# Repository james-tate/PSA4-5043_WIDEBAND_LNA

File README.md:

#PSA4-5043 LNA with onboard Bias tee designed for use with RTL SDR dongles, hackrf, or other SDR. LNA has two power options, USB mini or power from inline. There is also an option for an on-board wideband bias tee and bandpass filter.

"The current board design needs a series resistor between J1 and LED1 in order for the LED to operate. I will redesign the board soon to accommodate the changes. If you have the current board design, the trace can be cut betweeen the components and a 470ohm resistor can be put in its place."

[PSA4-5043 ](http://www.minicircuits.com/pdfs/PSA4-5043+.pdf) -- .05 to 4GHz  

[TCBT-14+ Bias Tee](http://www.minicircuits.com/pdfs/TCBT-14+.pdf) -- 10MHz to 10GHz  

[Optional bandpass filter](http://www.minicircuits.com/products/filters_sm_bandpass.shtml). 

<a href="https://oshpark.com/shared_projects/NCNWYLgf"></img></a> You can order the 3 copies of the board from Oshpark for $4.75 

Feel free to contact me  if any questions or if you suggest changes.

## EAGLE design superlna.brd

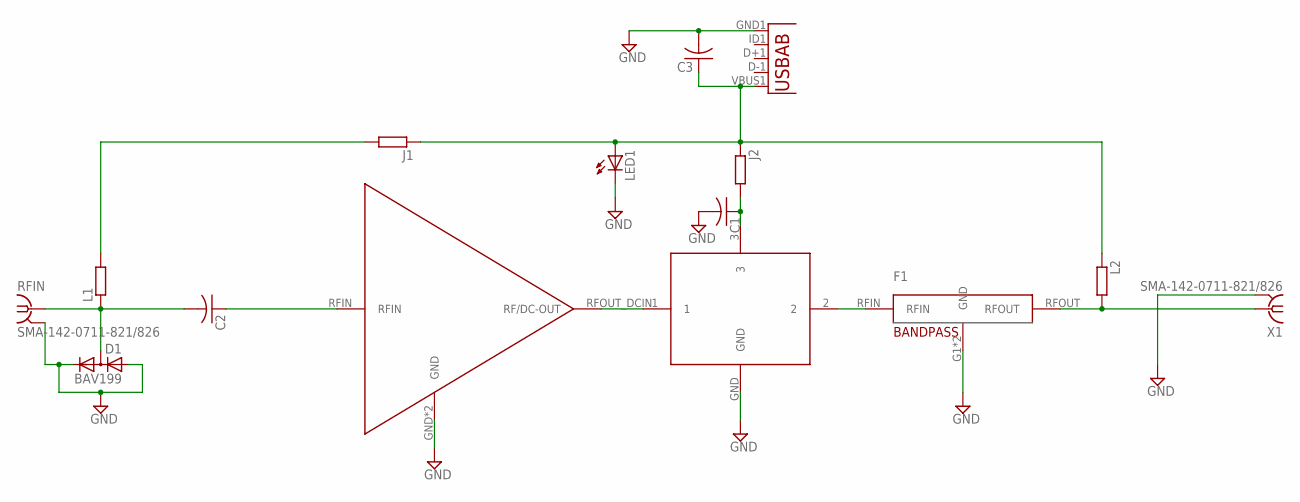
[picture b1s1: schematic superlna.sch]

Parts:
C1, C2, C3: C-USC0402; C0402
D1: BAV199; SOT23
F1: BANDPASS; FV1206
J1, J2: R-EU_R0805; R0805
L1, L2: R-EU_R0805; R0805
LED1: LED_ESML0603; LED_SML0603
LNA: AMP; SOC-343
POWER: USB""; USB-MICRO-SMD
RFIN: SMA-142-0711-821/826; J502-ND-142-0711-821/826
U1: BIASTEE; GU1414
X1: SMA-142-0711-821/826; J502-ND-142-0711-821/826

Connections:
BIASPOWER: C1.1, J2.2, U1.3
GND: C1.2, C3.2, D1.1 (A), D1.2 (C), F1.G1 (GND), F1.G2 (GND), LED1.C, LNA.GND, LNA.GND1 (GND), POWER.GND1 (GND), RFIN.G@1 (2), RFIN.G@2 (2), RFIN.G@3 (2), RFIN.G@4 (2), U1.GND, X1.G@1 (2), X1.G@2 (2), X1.G@3 (2), X1.G@4 (2)
unnamed: C2.1, LNA.RFIN
unnamed: LNA.RFOUT_DCIN (RF/DC-OUT), U1.1
unnamed: J1.2, L1.2
PWRIN: C3.1, J1.1, J2.1, L2.1, LED1.A, POWER.VBUS1 (VBUS)
RFIN: C2.2, D1.3 (AC), L1.1, RFIN.1
RFOUT: F1.RFOUT, L2.2, X1.1
RFOUT1: F1.RFIN, U1.2

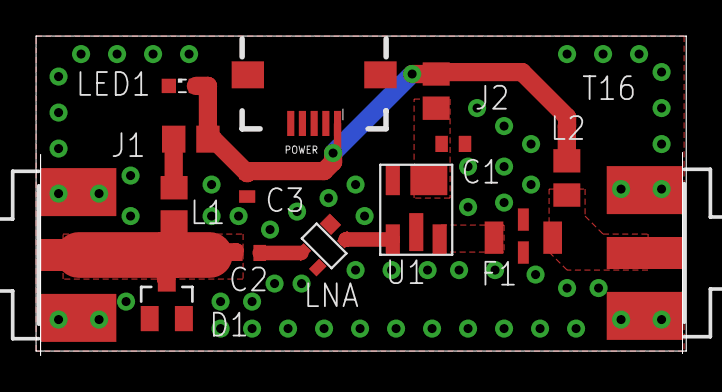
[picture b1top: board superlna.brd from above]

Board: 2 copper layers, 36.1 x 17.7 mm, 15 parts (0 on the bottom side), 9 nets.

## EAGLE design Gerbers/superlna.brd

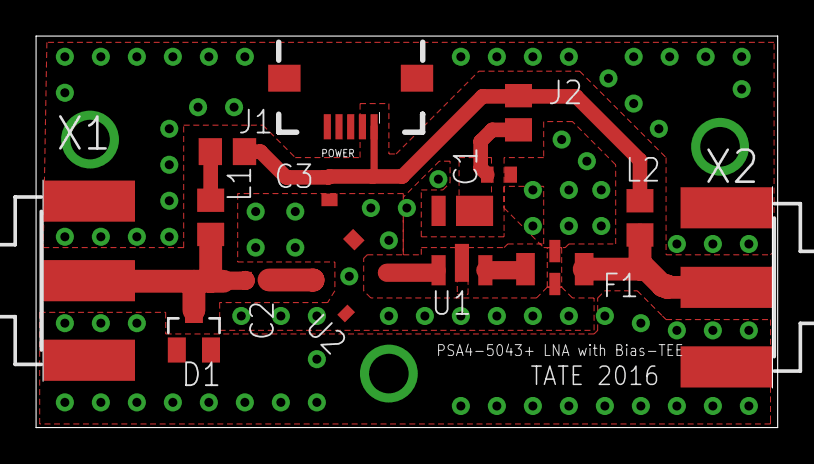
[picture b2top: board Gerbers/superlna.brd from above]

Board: 2 copper layers, 41.2 x 21.8 mm, 14 parts (0 on the bottom side), 9 nets.

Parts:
C1, C2, C3: C0402
D1: BAV199; SOT23
F1: BANDPASS; FV1206
J1, J2: R0805
L1, L2: R0805
POWER: USB-MICRO-SMD
U1: BIASTEE; GU1414
U2: AMP; SOC-343
X1, X2: SMA-142-0701-801/806; J502-ND-142-0701-801/806

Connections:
BIASPOWER: C1.1, J2.2, U1.3
GND: C1.2, C3.2, D1.1, D1.2, F1.G1, F1.G2, POWER.GND1, U1.GND, U2.GND, U2.GND1, X1.G@1, X1.G@2, X1.G@3, X1.G@4, X2.G@1, X2.G@2, X2.G@3, X2.G@4
unnamed: C2.1, U2.RFIN
unnamed: C3.1, J1.1, J2.1, L2.1, POWER.VBUS1
unnamed: U1.1, U2.RFOUT_DCIN
unnamed: F1.RFIN, U1.2
unnamed: J1.2, L1.2
RFIN: C2.2, D1.3, L1.1, X1.1
RFOUT: F1.RFOUT, L2.2, X2.1

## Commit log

2016-10-28 head
2016-10-28 started
2016-10-30 V1.0
2016-10-30 License
2016-11-10 changed some traces for better 50ohm
2016-11-14 changes to V1
2016-12-02 Update README.md
    Added link to oshpark order
